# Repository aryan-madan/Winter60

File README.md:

# Winter60

# Backstory

I am a keyboard addict. I've been in love with the mechanical keyboard community for almost 6 years now.

I made my first keyboard in Blueprint, which also my first ever hardware project. I made a 65% hotswap keyboard for it, which had design flaws and ended up not fully working. I wanted to redeem myself by giving myself another shot and making another keyboard. So, I decided on making a 60% keyboard with 4 dedicated macro keys.

# Layout

The Winter has a 60% layout with 4 macro keys in the left.
The macro keys provide dedicated support for macros, which can be bound to in-game callouts, hotkeys, etc.

On the right side are the MCU and screen, which acts like a tamagotchi!

# Firmware

The firmware for the Winter is located in the '/firmware' directory.
The Winter60 uses QMK for the firmware.

# Schematics & PCB

## Schematics

## PCB

# CAD

The case was modeled using Shapr3D.
You can view the model online here: [Shapr3D](https://app.shapr3d.com/p/aef21a27-1508-4fc5-99ec-32f52b3ec96d)

The plate was generated from a plate generator.

# BOM

The total bill of materials totaled to about $132.12.
You can see the complete [BOM.csv](BOM.csv)

Made with ❤️ by Ary

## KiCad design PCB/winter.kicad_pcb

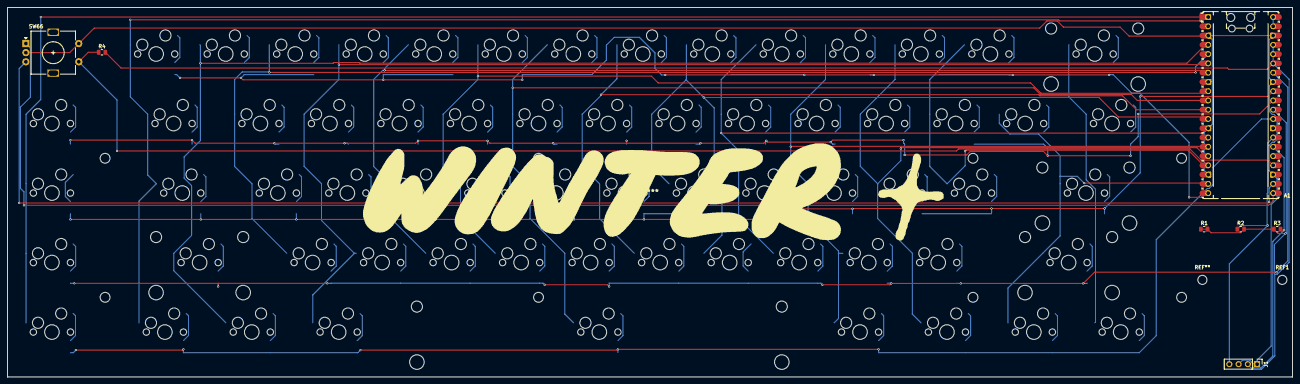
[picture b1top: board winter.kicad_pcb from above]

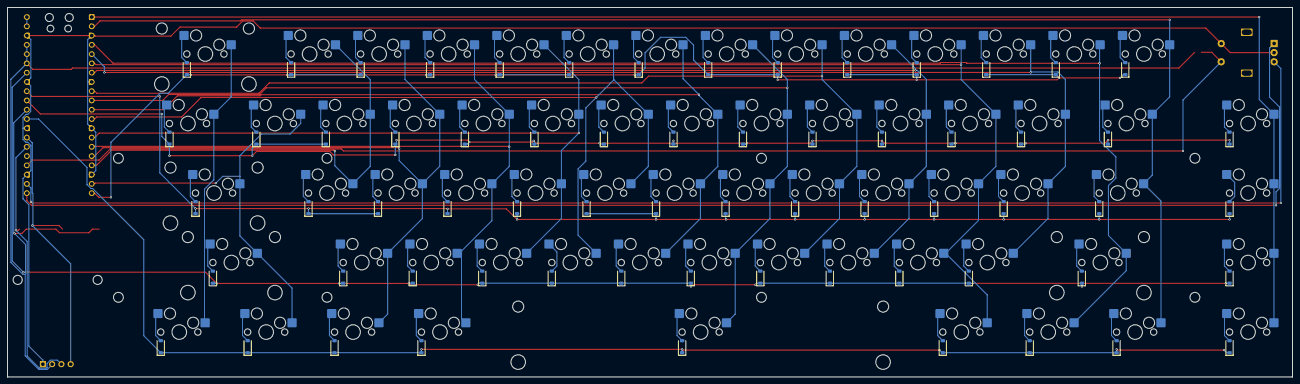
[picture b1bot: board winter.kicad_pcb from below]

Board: 2 copper layers, 352.1 x 101.2 mm, 151 parts (65 on the bottom side), 94 nets.

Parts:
A1: RaspberryPi_Pico; RaspberryPi_Pico_Common_Unspecified
D1, D2, D3, D4, D5, D6, D7, D8, D9, D10, D11, D12, D13, D14, D15, D16, D17, D18, D19, D20, D21, D22, D23, D24, D25, D26, D27, D28, D29, D30, D31, D32, D33, D34, D35, D36, D37, D38, D39, D40, D41, D42, D43, D44, D45, D46, D47, D48, D49, D50, D51, D52, D53, D54, D55, D56, D57, D58, D59, D60, D61, D62, D63, D64, D65: D; D_SOD-123
H1, H2, H3, H4, H5, H6, H10, H11: MountingHole_2.7mm_M2.5_Clean
J1: Conn_01x04; PinHeader_1x04_P2.54mm_Vertical
R1, R4: 10k; R_0805_2012Metric
R2, R3: 4.7k; R_0805_2012Metric
REF1: MountingHole_2.5mm
ST14, ST43, ST45, ST56: SW_stab; Stabilizer_Cherry_MX_2.00u
ST61: SW_stab; Stabilizer_Cherry_MX_6.25u
SW1, SW2, SW3, SW4, SW5, SW6, SW7, SW8, SW9, SW10, SW11, SW12, SW13, SW15, SW17, SW18, SW19, SW20, SW21, SW22, SW23, SW24, SW25, SW26, SW27, SW28, SW30, SW32, SW33, SW34, SW35, SW36, SW37, SW38, SW39, SW40, SW41, SW42, SW44, SW46, SW47, SW48, SW49, SW50, SW51, SW52, SW53, SW54, SW55, SW57: SW_Push; SW_Hotswap_Kailh_MX_1.00u
SW14: SW_Push; SW_Hotswap_Kailh_MX_2.00u
SW16, SW29: SW_Push; SW_Hotswap_Kailh_MX_1.50u
SW31: SW_Push; SW_Hotswap_Kailh_MX_1.75u
SW43, SW45: SW_Push; SW_Hotswap_Kailh_MX_2.25u
SW56: SW_Push; SW_Hotswap_Kailh_MX_2.75u
SW58, SW59, SW60, SW62, SW63, SW64, SW65: SW_Push; SW_Hotswap_Kailh_MX_1.25u
SW61: SW_Push; SW_Hotswap_Kailh_MX_6.25u
SW66: RotaryEncoder_Switch; RotaryEncoder_Alps_EC11E-Switch_Vertical_H20mm

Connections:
+3.3V: A1.30 (RUN), A1.35 (ADC_VREF), A1.36 (3V3), A1.37 (3V3_EN), J1.2, R1.1, R1.2, R2.2, R3.1, R4.2
+5V: A1.39 (VSYS), A1.40 (VBUS)
COL0: A1.1 (GPIO0), SW15.1, SW30.1, SW44.1, SW57.1
COL1: A1.2 (GPIO1), SW1.1, SW16.1, SW31.1, SW58.1
COL2: A1.4 (GPIO2), SW2.1, SW45.1, SW59.1
COL3: A1.5 (GPIO3), SW3.1, SW17.1, SW32.1, SW46.1
COL4: A1.6 (GPIO4), SW4.1, SW18.1, SW33.1, SW47.1, SW60.1
COL5: A1.7 (GPIO5), SW5.1, SW19.1, SW34.1, SW48.1
COL6: A1.9 (GPIO6), SW6.1, SW20.1, SW35.1, SW49.1
COL7: A1.10 (GPIO7), SW7.1, SW21.1, SW36.1, SW50.1, SW61.1
COL8: A1.11 (GPIO8), SW8.1, SW22.1, SW37.1, SW51.1
COL9: A1.12 (GPIO9), SW9.1, SW23.1, SW38.1, SW52.1
COL10: A1.14 (GPIO10), SW10.1, SW24.1, SW39.1, SW53.1
COL11: A1.15 (GPIO11), SW11.1, SW25.1, SW40.1, SW54.1, SW62.1
COL12: A1.16 (GPIO12), SW12.1, SW26.1, SW41.1, SW55.1, SW63.1
COL13: A1.17 (GPIO13), SW13.1, SW27.1, SW42.1
COL14: A1.19 (GPIO14), SW28.1, SW43.1, SW56.1, SW64.1
COL15: SW14.1, SW29.1, SW65.1
ENC_A: A1.21 (GPIO16), SW66.A
ENC_B: A1.22 (GPIO17), SW66.B
ENC_SW: A1.24 (GPIO18), R4.1, SW66.S1
GND: A1.3 (GND), A1.8 (GND), A1.13 (GND), A1.18 (GND), A1.23 (GND), A1.28 (GND), A1.33 (AGND), A1.38 (GND), J1.1, SW66.C, SW66.S2
unnamed: D1.2 (A), SW1.2
unnamed: D2.2 (A), SW2.2
unnamed: D3.2 (A), SW3.2
unnamed: D4.2 (A), SW4.2
unnamed: D5.2 (A), SW5.2
unnamed: D6.2 (A), SW6.2
unnamed: D7.2 (A), SW7.2
unnamed: D8.2 (A), SW8.2
unnamed: D9.2 (A), SW9.2
unnamed: D10.2 (A), SW10.2
unnamed: D11.2 (A), SW11.2
unnamed: D12.2 (A), SW12.2
unnamed: D13.2 (A), SW13.2
unnamed: D14.2 (A), SW14.2
unnamed: D15.2 (A), SW15.2
unnamed: D16.2 (A), SW16.2
unnamed: D17.2 (A), SW17.2
unnamed: D18.2 (A), SW18.2
unnamed: D19.2 (A), SW19.2
unnamed: D20.2 (A), SW20.2
unnamed: D21.2 (A), SW21.2
unnamed: D22.2 (A), SW22.2
unnamed: D23.2 (A), SW23.2
unnamed: D24.2 (A), SW24.2
unnamed: D25.2 (A), SW25.2
unnamed: D26.2 (A), SW26.2
unnamed: D27.2 (A), SW27.2
unnamed: D28.2 (A), SW28.2
unnamed: D29.2 (A), SW29.2
unnamed: D30.2 (A), SW30.2
unnamed: D31.2 (A), SW31.2
unnamed: D32.2 (A), SW32.2
unnamed: D33.2 (A), SW33.2
unnamed: D34.2 (A), SW34.2
unnamed: D35.2 (A), SW35.2
unnamed: D36.2 (A), SW36.2
unnamed: D37.2 (A), SW37.2
unnamed: D38.2 (A), SW38.2
unnamed: D39.2 (A), SW39.2
unnamed: D40.2 (A), SW40.2
unnamed: D41.2 (A), SW41.2
unnamed: D42.2 (A), SW42.2
unnamed: D43.2 (A), SW43.2
unnamed: D44.2 (A), SW44.2
unnamed: D45.2 (A), SW45.2
unnamed: D46.2 (A), SW46.2
unnamed: D47.2 (A), SW47.2
unnamed: D48.2 (A), SW48.2
unnamed: D49.2 (A), SW49.2
unnamed: D50.2 (A), SW50.2
unnamed: D51.2 (A), SW51.2
unnamed: D52.2 (A), SW52.2
unnamed: D53.2 (A), SW53.2
unnamed: D54.2 (A), SW54.2
unnamed: D55.2 (A), SW55.2
unnamed: D56.2 (A), SW56.2
unnamed: D57.2 (A), SW57.2
unnamed: D58.2 (A), SW58.2
unnamed: D59.2 (A), SW59.2
unnamed: D60.2 (A), SW60.2
unnamed: D61.2 (A), SW61.2
unnamed: D62.2 (A), SW62.2
unnamed: D63.2 (A), SW63.2
unnamed: D64.2 (A), SW64.2
unnamed: D65.2 (A), SW65.2
ROW0: A1.20 (GPIO15), D1.1 (K), D2.1 (K), D3.1 (K), D4.1 (K), D5.1 (K), D6.1 (K), D7.1 (K), D8.1 (K), D9.1 (K), D10.1 (K), D11.1 (K), D12.1 (K), D13.1 (K), D14.1 (K)
ROW1: A1.31 (GPIO26_ADC0), D15.1 (K), D16.1 (K), D17.1 (K), D18.1 (K), D19.1 (K), D20.1 (K), D21.1 (K), D22.1 (K), D23.1 (K), D24.1 (K), D25.1 (K), D26.1 (K), D27.1 (K), D28.1 (K), D29.1 (K)
ROW2: A1.32 (GPIO27_ADC1), D30.1 (K), D31.1 (K), D32.1 (K), D33.1 (K), D34.1 (K), D35.1 (K), D36.1 (K), D37.1 (K), D38.1 (K), D39.1 (K), D40.1 (K), D41.1 (K), D42.1 (K), D43.1 (K)
ROW3: A1.34 (GPIO28_ADC2), D44.1 (K), D45.1 (K), D46.1 (K), D47.1 (K), D48.1 (K), D49.1 (K), D50.1 (K), D51.1 (K), D52.1 (K), D53.1 (K), D54.1 (K), D55.1 (K), D56.1 (K)
ROW4: A1.29 (GPIO22), D57.1 (K), D58.1 (K), D59.1 (K), D60.1 (K), D61.1 (K), D62.1 (K), D63.1 (K), D64.1 (K), D65.1 (K)
SCL: A1.27 (GPIO21), J1.4, R2.1
SDA: A1.26 (GPIO20), J1.3, R3.2

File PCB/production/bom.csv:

Designator,Footprint,Quantity,Value,LCSC Part #
A1,RaspberryPi_Pico_Common_Unspecified,1,RaspberryPi_Pico,
"D1, D10, D11, D12, D13, D14, D15, D16, D17, D18, D19, D2, D20, D21, D22, D23, D24, D25, D26, D27, D28, D29, D3, D30, D31, D32, D33, D34, D35, D36, D37, D38, D39, D4, D40, D41, D42, D43, D44, D45, D46, D47, D48, D49, D5, D50, D51, D52, D53, D54, D55, D56, D57, D58, D59, D6, D60, D61, D62, D63, D64, D65, D7, D8, D9",D_SOD-123,65,D,
J1,PinHeader_1x04_P2.54mm_Vertical,1,Conn_01x04,
"R1, R4",0805,2,10k,
"R2, R3",0805,2,4.7k,
"SW1, SW10, SW11, SW12, SW13, SW15, SW17, SW18, SW19, SW2, SW20, SW21, SW22, SW23, SW24, SW25, SW26, SW27, SW28, SW3, SW30, SW32, SW33, SW34, SW35, SW36, SW37, SW38, SW39, SW4, SW40, SW41, SW42, SW44, SW46, SW47, SW48, SW49, SW5, SW50, SW51, SW52, SW53, SW54, SW55, SW57, SW6, SW7, SW8, SW9",SW_Hotswap_Kailh_MX_1.00u,50,SW_Push,
SW14,SW_Hotswap_Kailh_MX_2.00u,1,SW_Push,
"SW16, SW29",SW_Hotswap_Kailh_MX_1.50u,2,SW_Push,
SW31,SW_Hotswap_Kailh_MX_1.75u,1,SW_Push,
"SW43, SW45",SW_Hotswap_Kailh_MX_2.25u,2,SW_Push,
SW56,SW_Hotswap_Kailh_MX_2.75u,1,SW_Push,
"SW58, SW59, SW60, SW62, SW63, SW64, SW65",SW_Hotswap_Kailh_MX_1.25u,7,SW_Push,
SW61,SW_Hotswap_Kailh_MX_6.25u,1,SW_Push,
SW66,RotaryEncoder_Alps_EC11E-Switch_Vertical_H20mm,1,RotaryEncoder_Switch,

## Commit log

2026-05-10 Init
2026-05-10 Fix asset path in README.md
2026-05-13 fixed the firmware, and added a .uf2 file
2026-05-13 added pcb files
2026-05-25 open sauce :P, added journal, bom
2026-05-25 fixed image paths in journal
2026-05-26 recalculate and fix the bom
2026-05-27 added the case link and step file
2026-05-27 fix readme
2026-06-03 changed mcu and added screen and knob
2026-06-05 new firmware and case
2026-06-06 Finishing new pcb, remodelling and new bom
2026-06-06 Final Case
2026-06-06 Update Image
2026-06-07 new branding and silkscreen
